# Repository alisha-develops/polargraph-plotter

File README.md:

# polargraph-plotter
This is my first hands-on project as a prospective engineer — a Polargraph Plotter built from scratch to explore electronics, motors, and coding. It uses stepper motors controlled by an Arduino to draw patterns on a vertical surface, combining hardware and software in a single system.

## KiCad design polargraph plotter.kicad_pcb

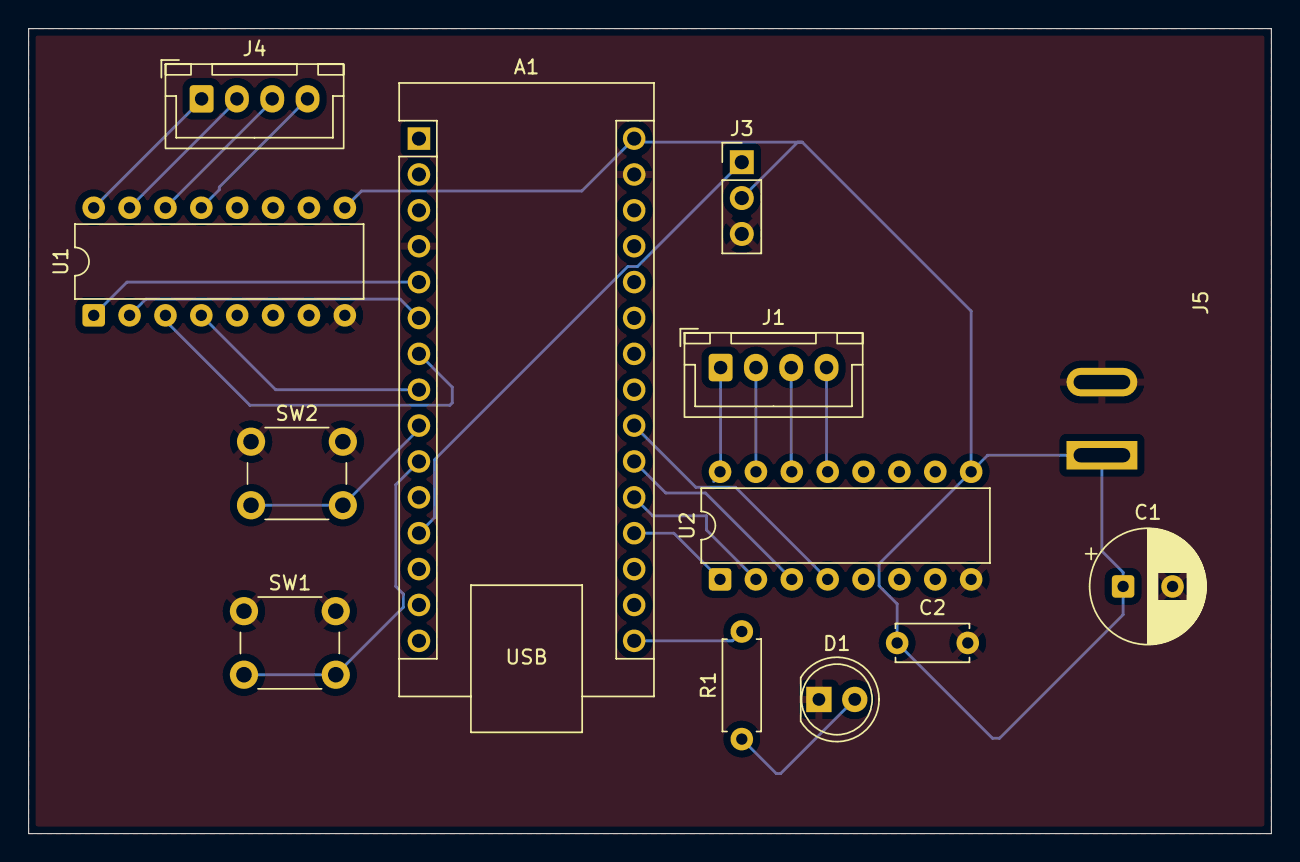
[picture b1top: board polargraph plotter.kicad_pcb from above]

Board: 2 copper layers, 88.0 x 57.0 mm, 13 parts (0 on the bottom side), 23 nets.

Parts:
A1: Arduino_Nano_Every; Arduino_Nano
C1: 470uF; CP_Radial_D8.0mm_P3.50mm
C2: 100nF; C_Disc_D5.0mm_W2.5mm_P5.00mm
D1: LED; LED_D5.0mm
J1, J4: Conn_01x04_Pin; JST_XH_B4B-XH-A_1x04_P2.50mm_Vertical
J3: Conn_01x03_Pin; PinHeader_1x03_P2.54mm_Vertical
J5: Barrel_Jack; BarrelJack_SwitchcraftConxall_RAPC10U_Horizontal
R1: 220R; R_Axial_DIN0207_L6.3mm_D2.5mm_P7.62mm_Horizontal
SW1, SW2: SW_Push; SW_PUSH_6mm
U1, U2: ULN2003; DIP-16_W7.62mm

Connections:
/+5v: A1.30 (VIN), C1.1, C2.1, J3.2, J5.1, U1.9 (COM), U2.9 (COM)
/MOT_L_1: A1.5 (D2), U1.1 (I1)
/MOT_L_2: A1.6 (D3), U1.2 (I2)
/MOT_L_3: A1.7 (D4), U1.3 (I3)
/MOT_L_4: A1.8 (D5), U1.4 (I4)
/MOT_R_1: A1.19 (A0), U2.1 (I1)
/MOT_R_2: A1.20 (A1), U2.2 (I2)
/MOT_R_3: A1.21 (A2), U2.3 (I3)
/MOT_R_4: A1.22 (A3), U2.4 (I4)
/SERVO_SIG: A1.12 (D9), J3.1
GND: A1.4 (GND), A1.29 (GND), C1.2, C2.2, D1.1 (K), J3.3, J5.2, SW1.1, SW2.1, U1.8 (GND), U2.8 (GND)
unnamed: A1.9 (D6), SW2.2
unnamed: A1.10 (D7), SW1.2
unnamed: A1.16 (SCK), R1.2
unnamed: D1.2 (A), R1.1
unnamed: J1.1, U2.16 (O1)
unnamed: J1.2, U2.15 (O2)
unnamed: J1.3, U2.14 (O3)
unnamed: J1.4, U2.13 (O4)
unnamed: J4.1, U1.16 (O1)
unnamed: J4.2, U1.15 (O2)
unnamed: J4.3, U1.14 (O3)
unnamed: J4.4, U1.13 (O4)
